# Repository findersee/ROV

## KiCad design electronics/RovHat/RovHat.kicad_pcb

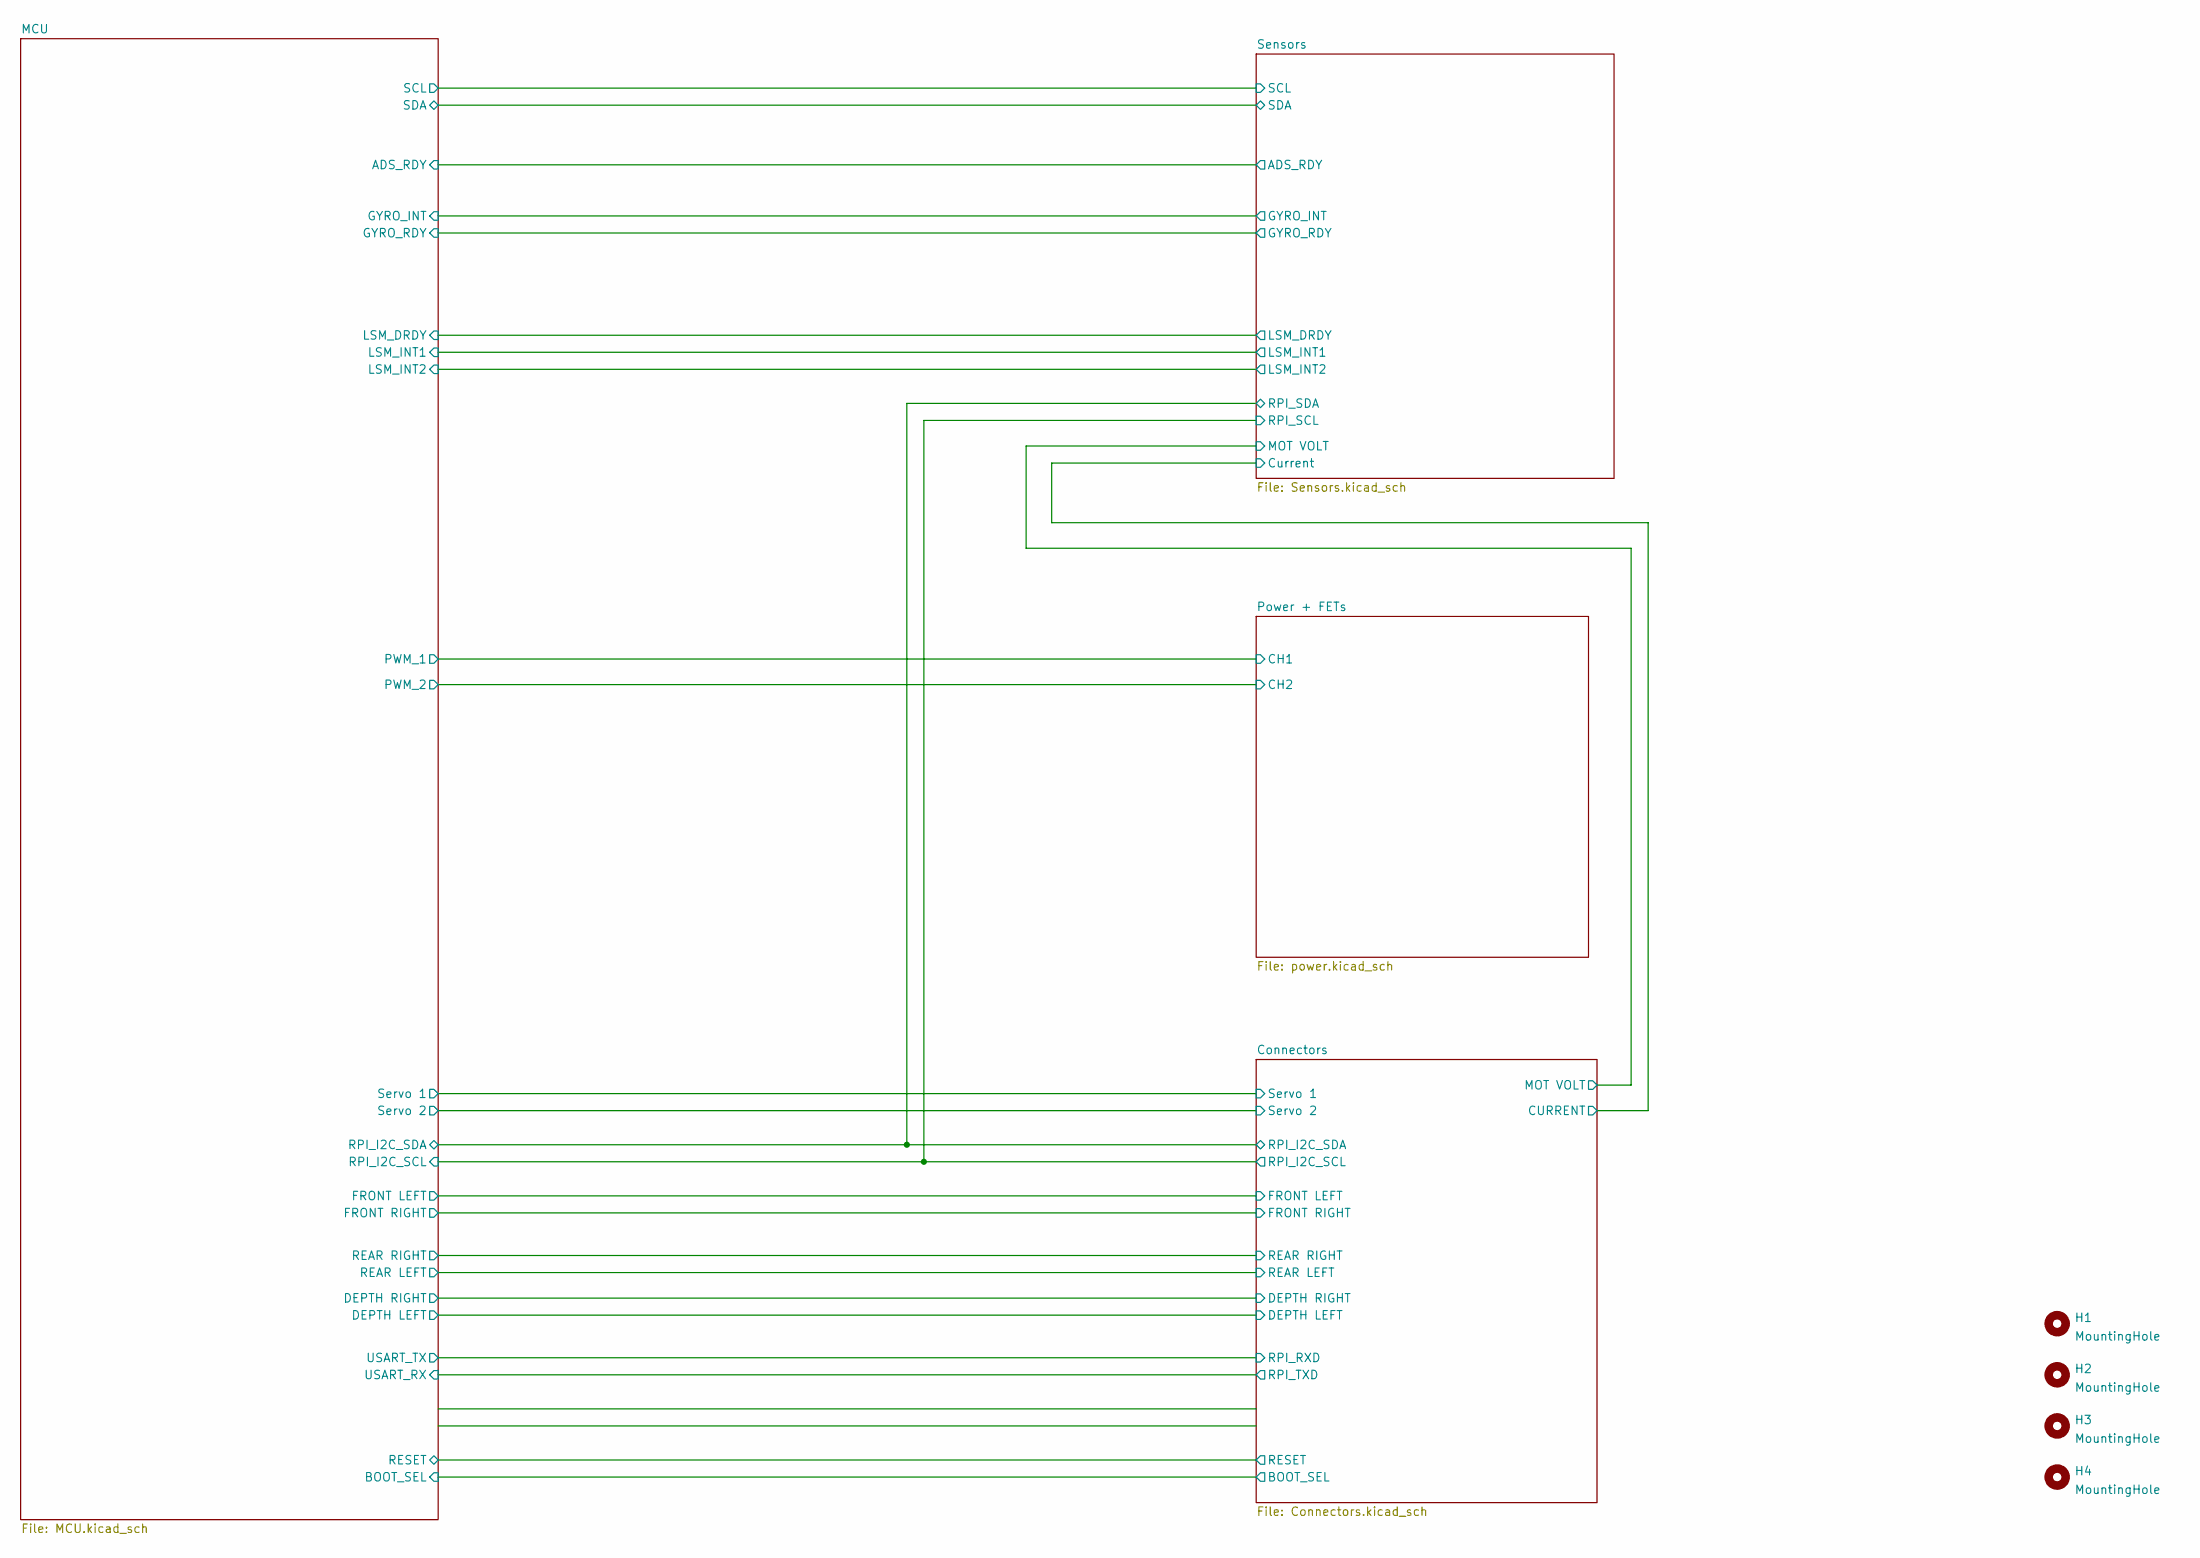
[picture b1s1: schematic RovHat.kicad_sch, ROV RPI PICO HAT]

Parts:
H1, H2, H3, H4: MountingHole; MountingHole_2.7mm_M2.5

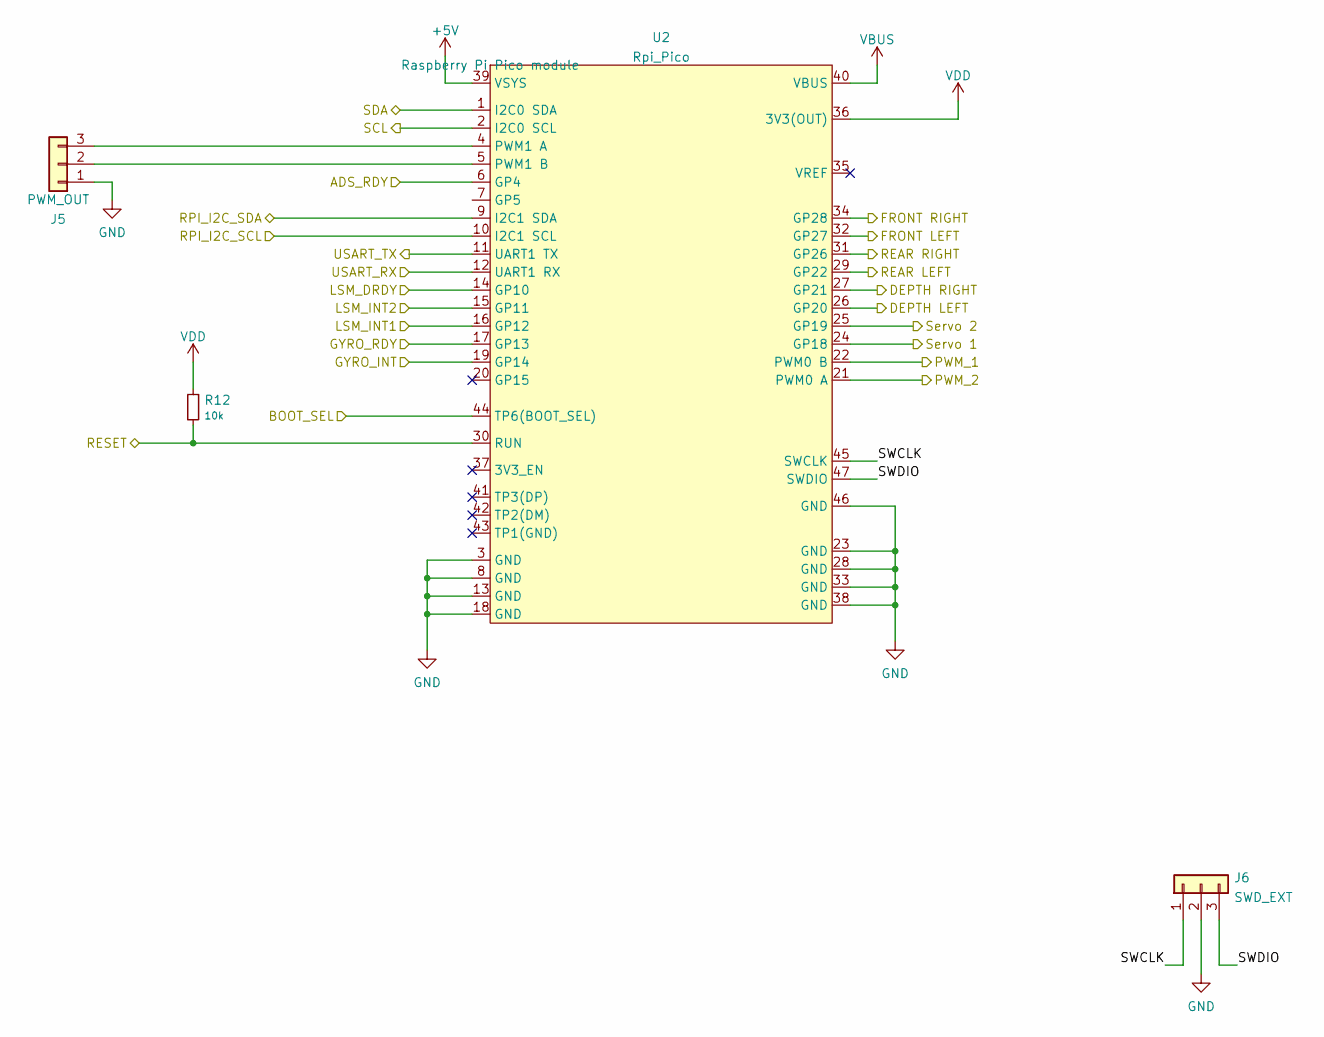
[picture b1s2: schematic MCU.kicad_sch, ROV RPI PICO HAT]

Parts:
J5: PWM_OUT; PinHeader_1x03_P2.54mm_Vertical
J6: SWD_EXT; JST_SH_BM03B-SRSS-TB_1x03-1MP_P1.00mm_Vertical
R12: 10k; R_0603_1608Metric
U2: Rpi_Pico; RP_PICO

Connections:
+5V: U2.39 (VSYS); also elsewhere on the board
/Connectors/BOOT_SEL: U2.44 (TP6(BOOT_SEL)); also elsewhere on the board
/Connectors/DEPTH LEFT: U2.26 (GP20); also elsewhere on the board
/Connectors/DEPTH RIGHT: U2.27 (GP21); also elsewhere on the board
/Connectors/FRONT LEFT: U2.32 (GP27); also elsewhere on the board
/Connectors/FRONT RIGHT: U2.34 (GP28); also elsewhere on the board
/Connectors/REAR LEFT: U2.29 (GP22); also elsewhere on the board
/Connectors/REAR RIGHT: U2.31 (GP26); also elsewhere on the board
/Connectors/RESET: R12.2, U2.30 (RUN); also elsewhere on the board
/Connectors/RPI_I2C_SCL: U2.10 (I2C1 SCL); also elsewhere on the board
/Connectors/RPI_I2C_SDA: U2.9 (I2C1 SDA); also elsewhere on the board
/Connectors/RPI_RXD: U2.11 (UART1 TX); also elsewhere on the board
/Connectors/RPI_TXD: U2.12 (UART1 RX); also elsewhere on the board
/Connectors/Servo 1: U2.24 (GP18); also elsewhere on the board
/Connectors/Servo 2: U2.25 (GP19); also elsewhere on the board
/MCU/ADS_RDY: U2.6 (GP4); also elsewhere on the board
/MCU/GYRO_INT: U2.19 (GP14); also elsewhere on the board
/MCU/GYRO_RDY: U2.17 (GP13); also elsewhere on the board
/MCU/LSM_DRDY: U2.14 (GP10); also elsewhere on the board
/MCU/LSM_INT1: U2.16 (GP12); also elsewhere on the board
/MCU/LSM_INT2: U2.15 (GP11); also elsewhere on the board
/MCU/PWM_1: U2.22 (PWM0 B); also elsewhere on the board
/MCU/PWM_2: U2.21 (PWM0 A); also elsewhere on the board
/MCU/SWCLK: J6.1, U2.45 (SWCLK)
/MCU/SWDIO: J6.3, U2.47 (SWDIO)
/Sensors/SCL: U2.2 (I2C0 SCL); also elsewhere on the board
/Sensors/SDA: U2.1 (I2C0 SDA); also elsewhere on the board
GND: J5.1, J6.2, U2.3 (GND), U2.8 (GND), U2.13 (GND), U2.18 (GND), U2.23 (GND), U2.28 (GND), U2.33 (GND), U2.38 (GND), U2.46 (GND); also elsewhere on the board
unnamed: J5.2, U2.5 (PWM1 B)
unnamed: J5.3, U2.4 (PWM1 A)
VBUS: U2.40 (VBUS)
VDD: R12.1, U2.36 (3V3(OUT)); also elsewhere on the board

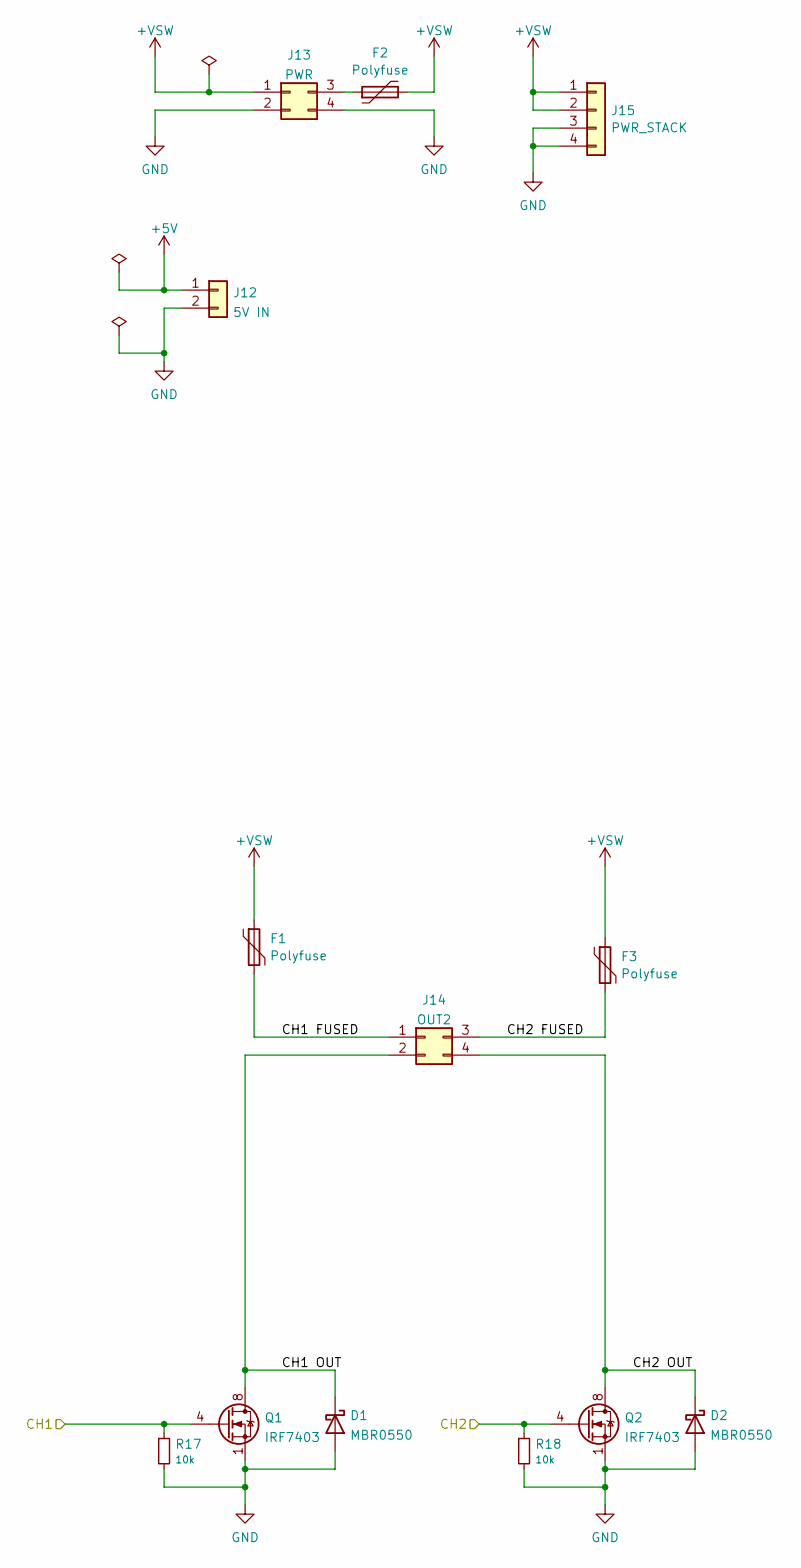
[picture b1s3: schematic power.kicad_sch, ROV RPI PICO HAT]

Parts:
D1, D2: MBR0550; D_SOD-123
F1, F2, F3: Polyfuse; Fuse_1206_3216Metric
J12: 5V IN; PinHeader_1x02_P2.54mm_Vertical
J13: PWR; PhoenixContact_MCV_1,5_4-G-3.5_1x04_P3.50mm_Vertical
J14: OUT2; PhoenixContact_MCV_1,5_4-G-3.5_1x04_P3.50mm_Vertical
J15: PWR_STACK; PinHeader_2x02_P2.54mm_Vertical
Q1, Q2: IRF7403; SOIC-8_3.9x4.9mm_P1.27mm
R17, R18: 10k; R_0603_1608Metric

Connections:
+5V: J12.1; also elsewhere on the board
+VSW: F1.1, F2.2, F3.1, J13.1, J15.1, J15.2
/MCU/PWM_1: Q1.4 (G), R17.1; also elsewhere on the board
/MCU/PWM_2: Q2.4 (G), R18.1; also elsewhere on the board
/Power + FETs/CH1 FUSED: F1.2, J14.1
/Power + FETs/CH1 OUT: D1.1 (K), J14.2, Q1.5 (D), Q1.6 (D), Q1.7 (D), Q1.8 (D)
/Power + FETs/CH2 FUSED: F3.2, J14.3
/Power + FETs/CH2 OUT: D2.1 (K), J14.4, Q2.5 (D), Q2.6 (D), Q2.7 (D), Q2.8 (D)
GND: D1.2 (A), D2.2 (A), J12.2, J13.2, J13.4, J15.3, J15.4, Q1.1 (S), Q1.2 (S), Q1.3 (S), Q2.1 (S), Q2.2 (S), Q2.3 (S), R17.2, R18.2; also elsewhere on the board
unnamed: F2.1, J13.3

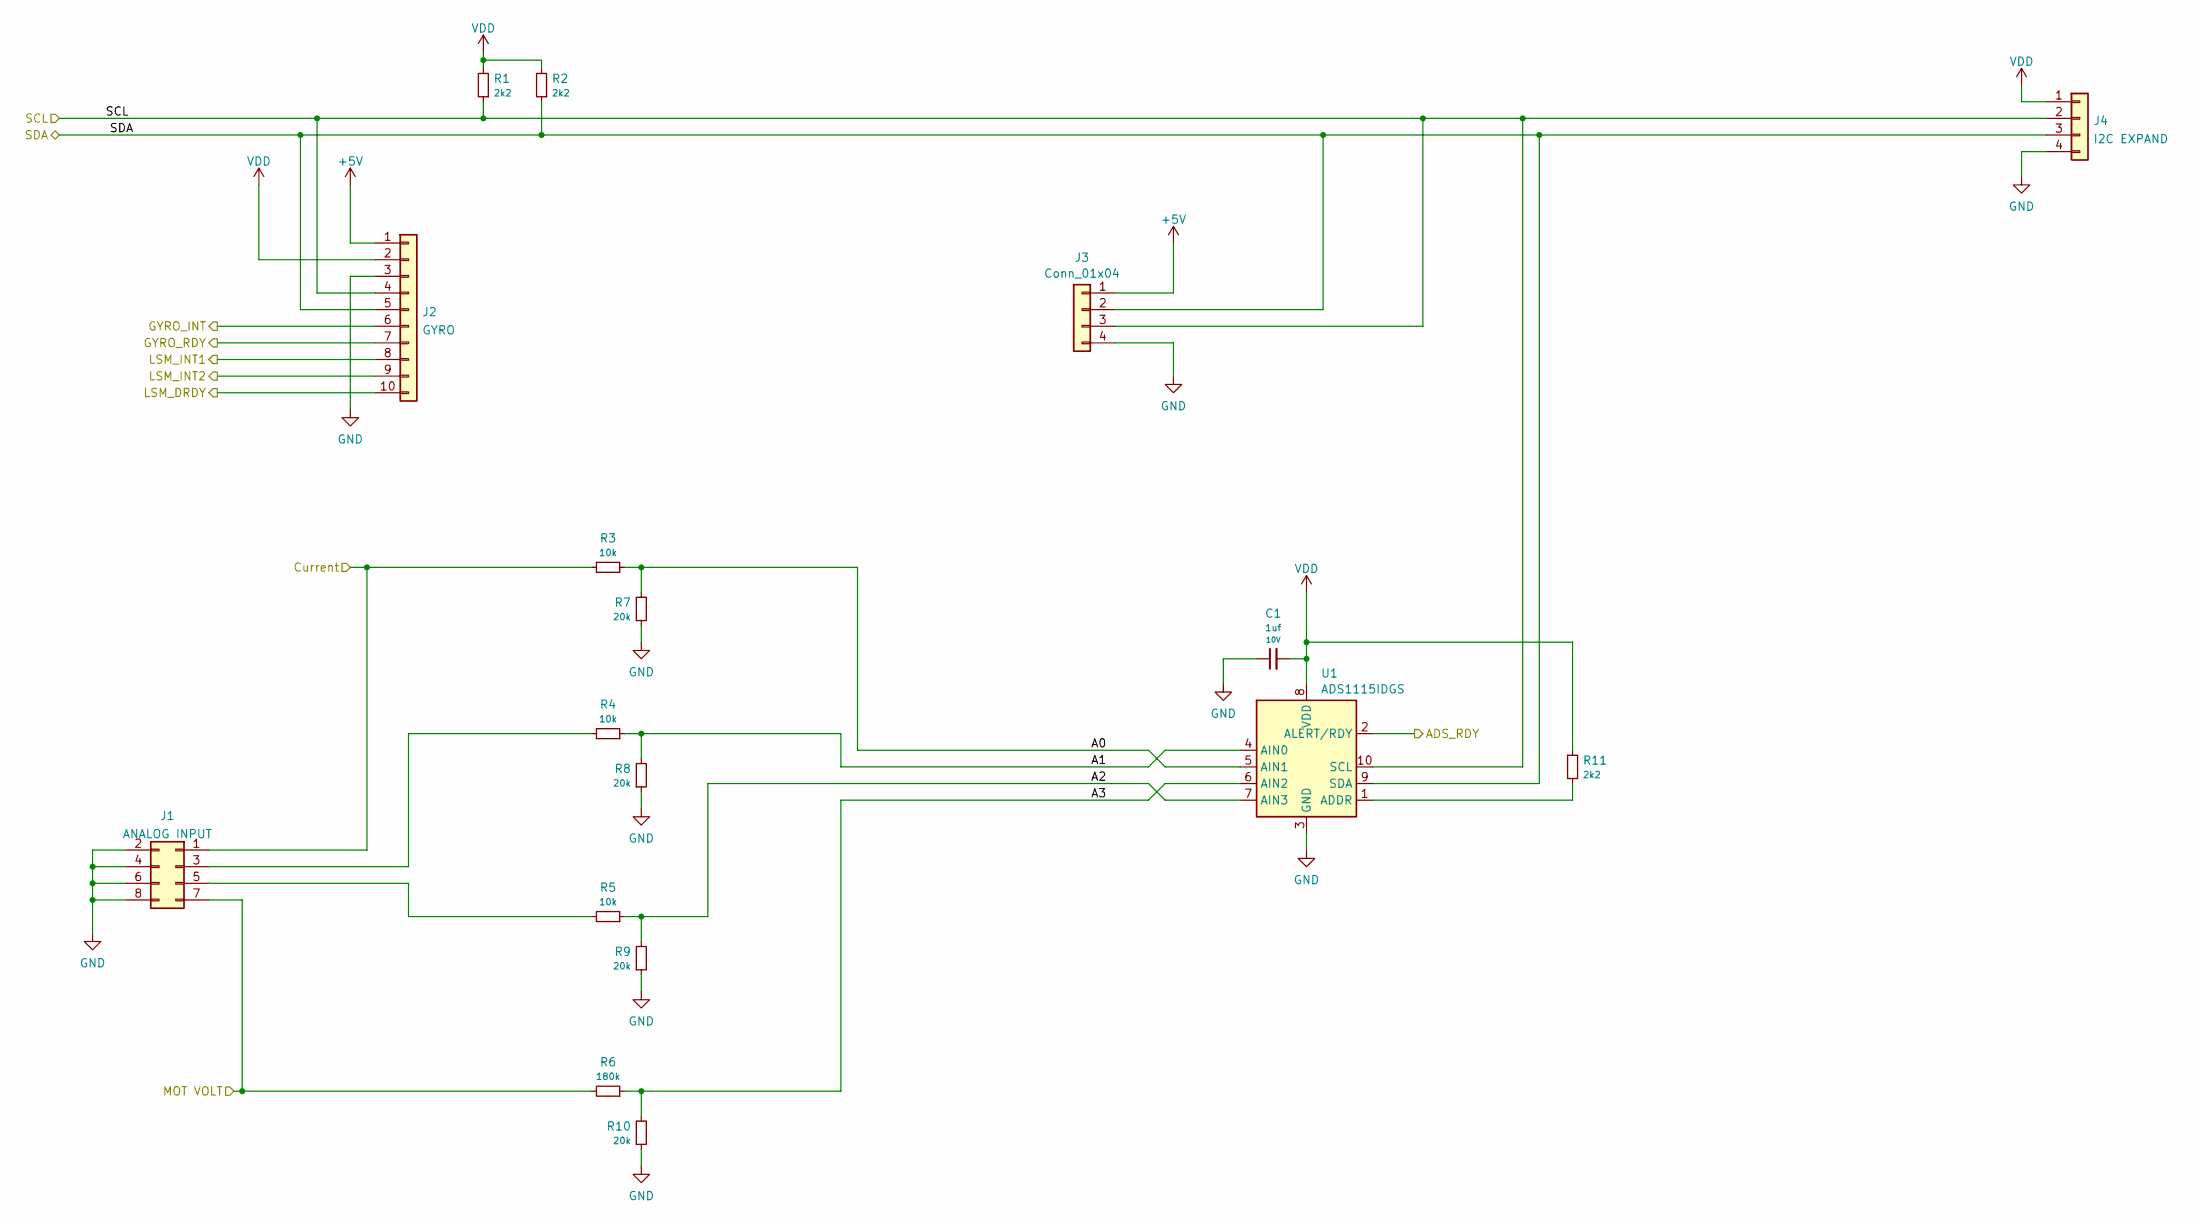
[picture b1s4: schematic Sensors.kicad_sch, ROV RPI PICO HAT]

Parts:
C1: 1uf; C_0603_1608Metric; Voltage 10V
J1: ANALOG INPUT; PinHeader_2x04_P2.54mm_Vertical
J2: GYRO; PinHeader_1x10_P2.54mm_Vertical
J3: Conn_01x04; Molex_PicoBlade_53398-0471_1x04-1MP_P1.25mm_Vertical
J4: I2C EXPAND; PinHeader_1x04_P2.54mm_Vertical
R1, R2, R11: 2k2; R_0603_1608Metric
R3, R4, R5: 10k; R_0603_1608Metric
R6: 180k; R_0603_1608Metric
R7, R8, R9, R10: 20k; R_0603_1608Metric
U1: ADS1115IDGS; TSSOP-10_3x3mm_P0.5mm

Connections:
+5V: J2.1, J3.1; also elsewhere on the board
/Connectors/CURRENT: J1.1, R3.2; also elsewhere on the board
/Connectors/MOT VOLT: J1.7, R6.2; also elsewhere on the board
/MCU/ADS_RDY: U1.2 (ALERT/RDY); also elsewhere on the board
/MCU/GYRO_INT: J2.6; also elsewhere on the board
/MCU/GYRO_RDY: J2.7; also elsewhere on the board
/MCU/LSM_DRDY: J2.10; also elsewhere on the board
/MCU/LSM_INT1: J2.8; also elsewhere on the board
/MCU/LSM_INT2: J2.9; also elsewhere on the board
/Sensors/A0: R3.1, R7.2, U1.5 (AIN1)
/Sensors/A1: R4.1, R8.2, U1.4 (AIN0)
/Sensors/A2: R5.1, R9.2, U1.7 (AIN3)
/Sensors/A3: R6.1, R10.2, U1.6 (AIN2)
/Sensors/SCL: J2.4, J3.3, J4.2, R1.1, U1.10 (SCL); also elsewhere on the board
/Sensors/SDA: J2.5, J3.2, J4.3, R2.1, U1.9 (SDA); also elsewhere on the board
GND: C1.1, J1.2, J1.4, J1.6, J1.8, J2.3, J3.4, J4.4, R7.1, R8.1, R9.1, R10.1, U1.3 (GND); also elsewhere on the board
unnamed: J1.3, R4.2
unnamed: J1.5, R5.2
unnamed: R11.2, U1.1 (ADDR)
VDD: C1.2, J2.2, J4.1, R1.2, R2.2, R11.1, U1.8 (VDD); also elsewhere on the board

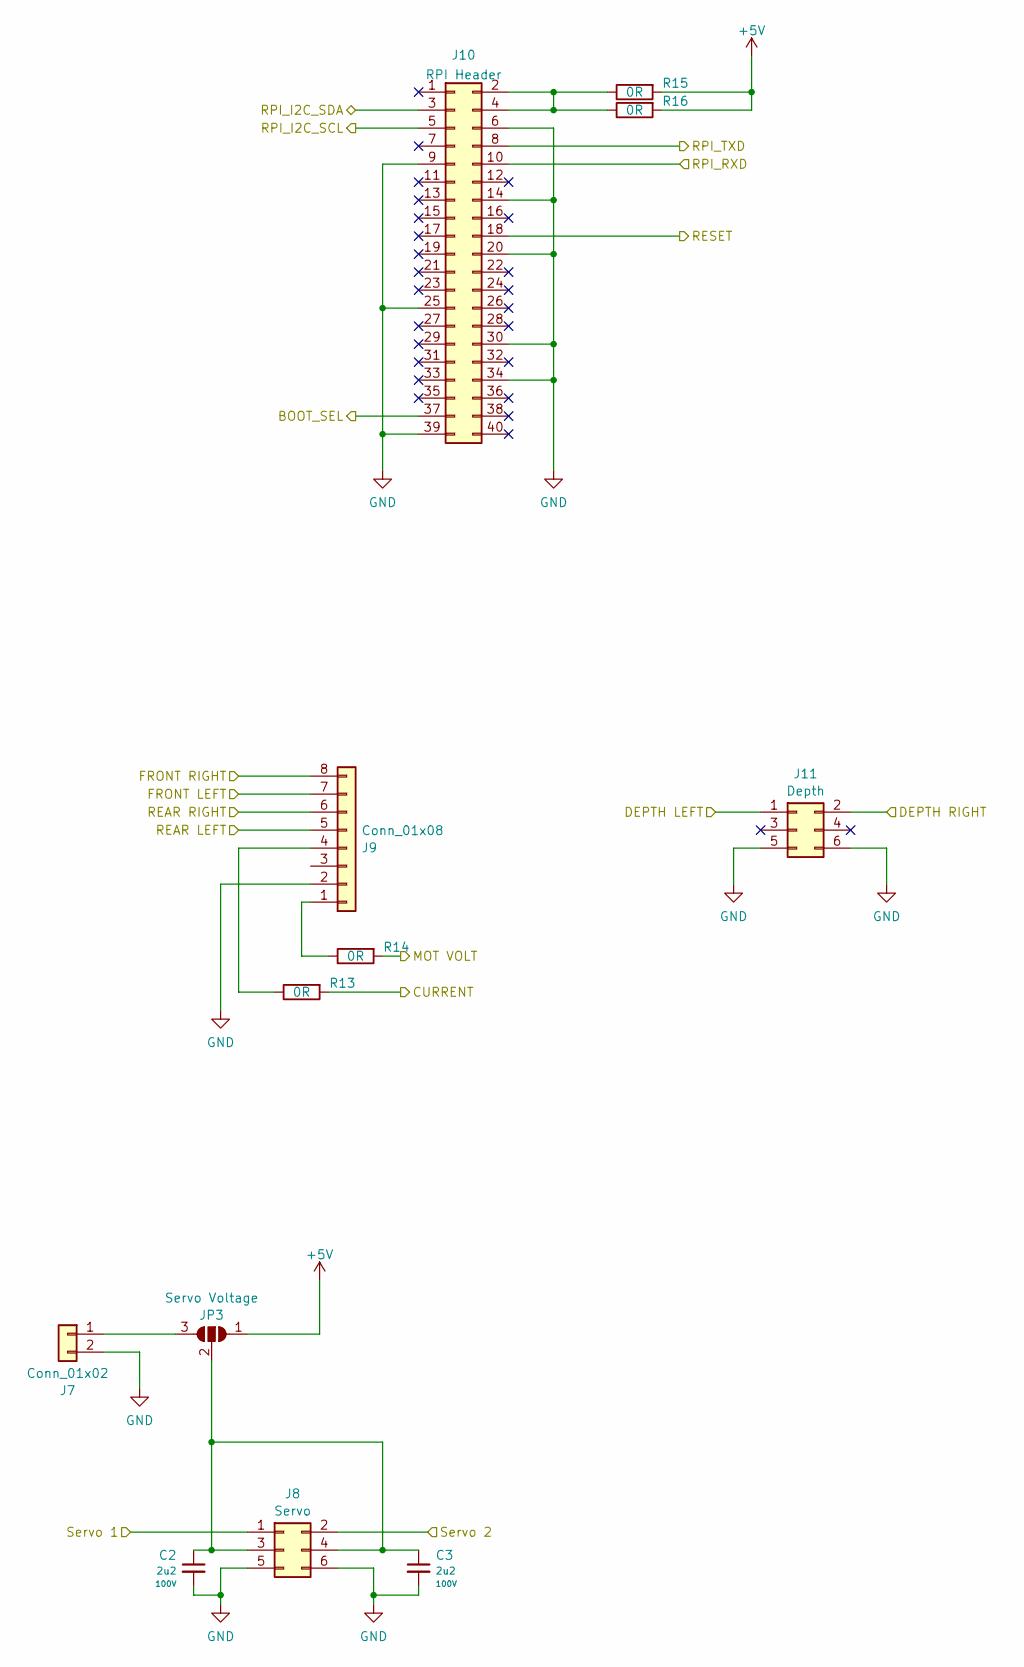
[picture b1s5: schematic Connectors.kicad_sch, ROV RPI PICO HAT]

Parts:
C2, C3: 2u2; C_0805_2012Metric; Voltage 100V
J7: Conn_01x02; PinHeader_2x01_P2.54mm_Vertical
J8: Servo; PinHeader_2x03_P2.54mm_Vertical
J9: Conn_01x08; JST_SH_SM08B-SRSS-TB_1x08-1MP_P1.00mm_Horizontal
J10: RPI Header; PinHeader_2x20_P2.54mm_Vertical
J11: Depth; PinHeader_2x03_P2.54mm_Vertical
JP3: Servo Voltage; 0402_Jumper_3pin
R13, R14, R15, R16: 0R; R_0603_1608Metric

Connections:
+5V: JP3.1 (A), R15.2, R16.2; also elsewhere on the board
/Connectors/BOOT_SEL: J10.37; also elsewhere on the board
/Connectors/CURRENT: R13.2; also elsewhere on the board
/Connectors/DEPTH LEFT: J11.1; also elsewhere on the board
/Connectors/DEPTH RIGHT: J11.2; also elsewhere on the board
/Connectors/FRONT LEFT: J9.7; also elsewhere on the board
/Connectors/FRONT RIGHT: J9.8; also elsewhere on the board
/Connectors/MOT VOLT: R14.2; also elsewhere on the board
/Connectors/REAR LEFT: J9.5; also elsewhere on the board
/Connectors/REAR RIGHT: J9.6; also elsewhere on the board
/Connectors/RESET: J10.18; also elsewhere on the board
/Connectors/RPI_I2C_SCL: J10.5; also elsewhere on the board
/Connectors/RPI_I2C_SDA: J10.3; also elsewhere on the board
/Connectors/RPI_RXD: J10.10; also elsewhere on the board
/Connectors/RPI_TXD: J10.8; also elsewhere on the board
/Connectors/Servo 1: J8.1; also elsewhere on the board
/Connectors/Servo 2: J8.2; also elsewhere on the board
GND: C2.2, C3.2, J7.2, J8.5, J8.6, J9.2, J10.6, J10.9, J10.14, J10.20, J10.25, J10.30, J10.34, J10.39, J11.5, J11.6; also elsewhere on the board
unnamed: J7.1, JP3.3 (B)
unnamed: C2.1, C3.1, J8.3, J8.4, JP3.2 (C)
unnamed: J9.1, R14.1
unnamed: J9.4, R13.1
unnamed: J10.2, J10.4, R15.1, R16.1

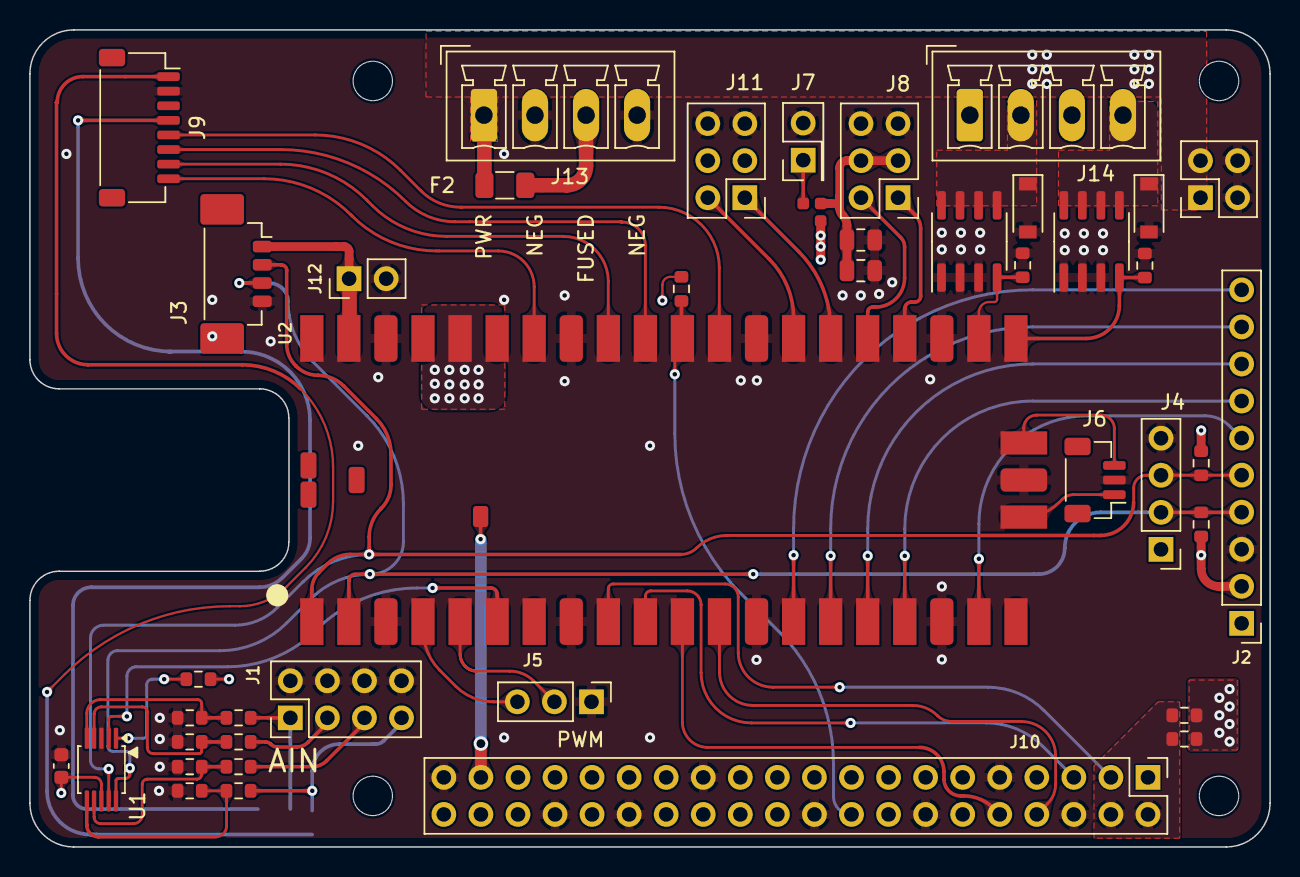
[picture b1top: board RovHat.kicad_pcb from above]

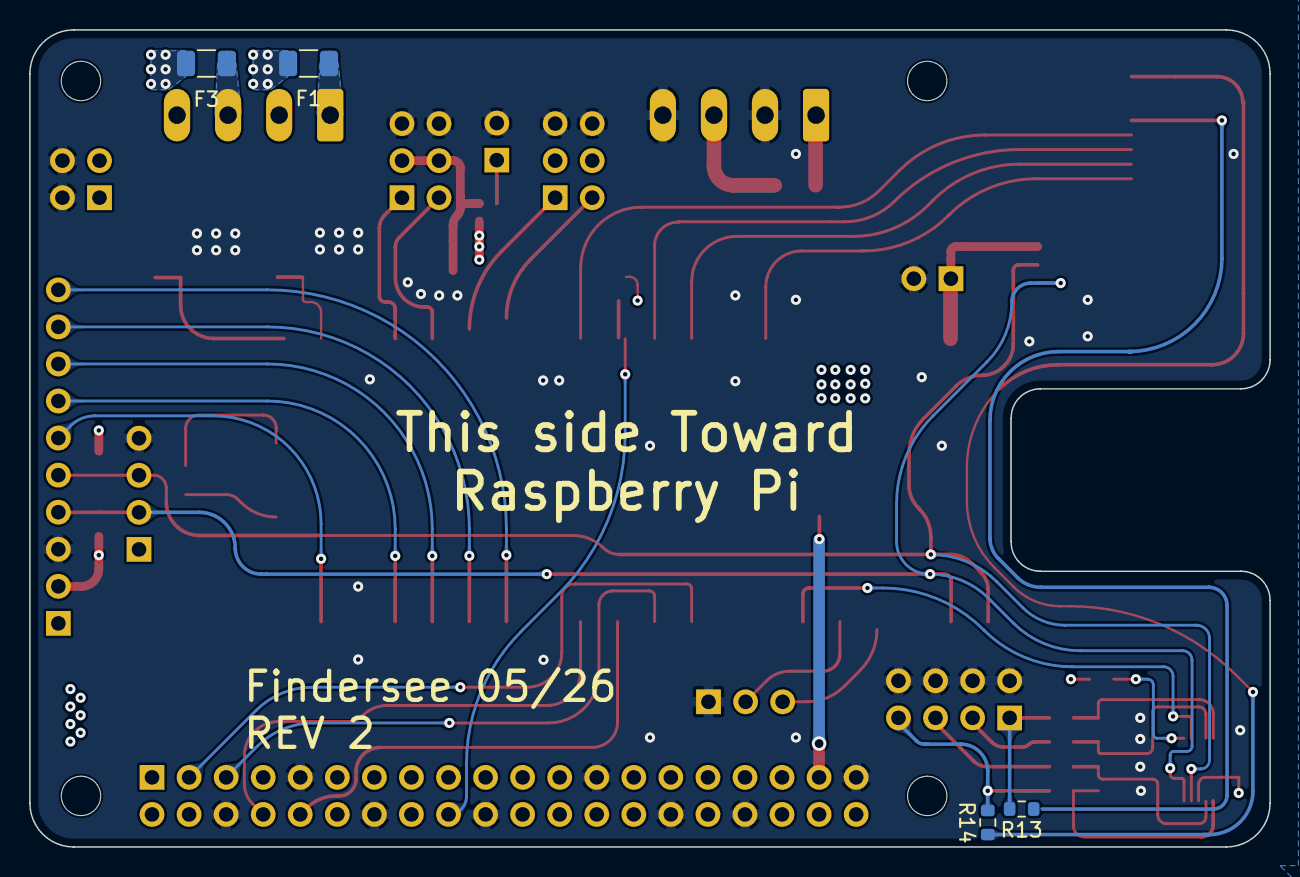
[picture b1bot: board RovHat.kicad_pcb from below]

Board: 4 copper layers, 85.0 x 56.0 mm, 50 parts (4 on the bottom side), 51 nets.

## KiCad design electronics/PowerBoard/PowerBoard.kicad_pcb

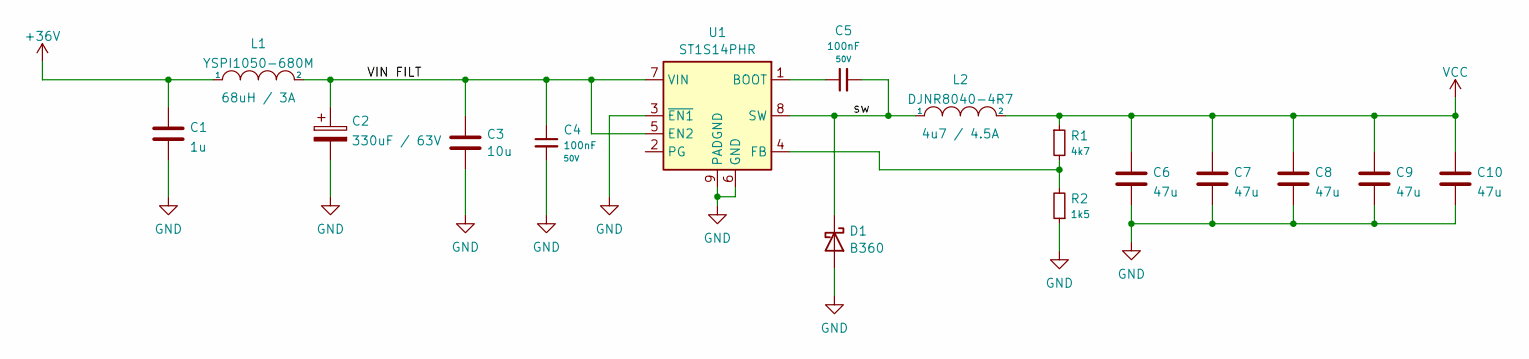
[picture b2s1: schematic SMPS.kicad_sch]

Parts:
C1: 1u; C_0805_2012Metric
C2: 330uF / 63V; CP_Elec_10x12.5
C3: 10u; C_0805_2012Metric
C4, C5: 100nF; C_0603_1608Metric; Voltage 50V
C6, C7, C8, C9, C10: 47u; C_0805_2012Metric
D1: B360; D_SMC
L1: YSPI1050-680M; YSPI1050; JLC C497902
L2: DJNR8040-4R7; IND_BOURNS_SRN8040; JLC C497902
R1: 4k7; R_0603_1608Metric
R2: 1k5; R_0603_1608Metric
U1: ST1S14PHR; TI_SO-PowerPAD-8

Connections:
+36V: C1.1, L1.1; also elsewhere on the board
/SMPS/VIN FILT: C2.1, C3.1, C4.1, L1.2, U1.5 (EN2), U1.7 (VIN)
/SMPS/sw: C5.2, D1.1 (K), L2.1, U1.8 (SW)
GND: C1.2, C2.2, C3.2, C4.2, C6.2, C7.2, C8.2, C9.2, C10.2, D1.2 (A), R2.1, U1.3 (~EN1), U1.6 (GND), U1.9 (PADGND); also elsewhere on the board
unnamed: C5.1, U1.1 (BOOT)
unnamed: R1.2, R2.2, U1.4 (FB)
VCC: C6.1, C7.1, C8.1, C9.1, C10.1, L2.2, R1.1; also elsewhere on the board

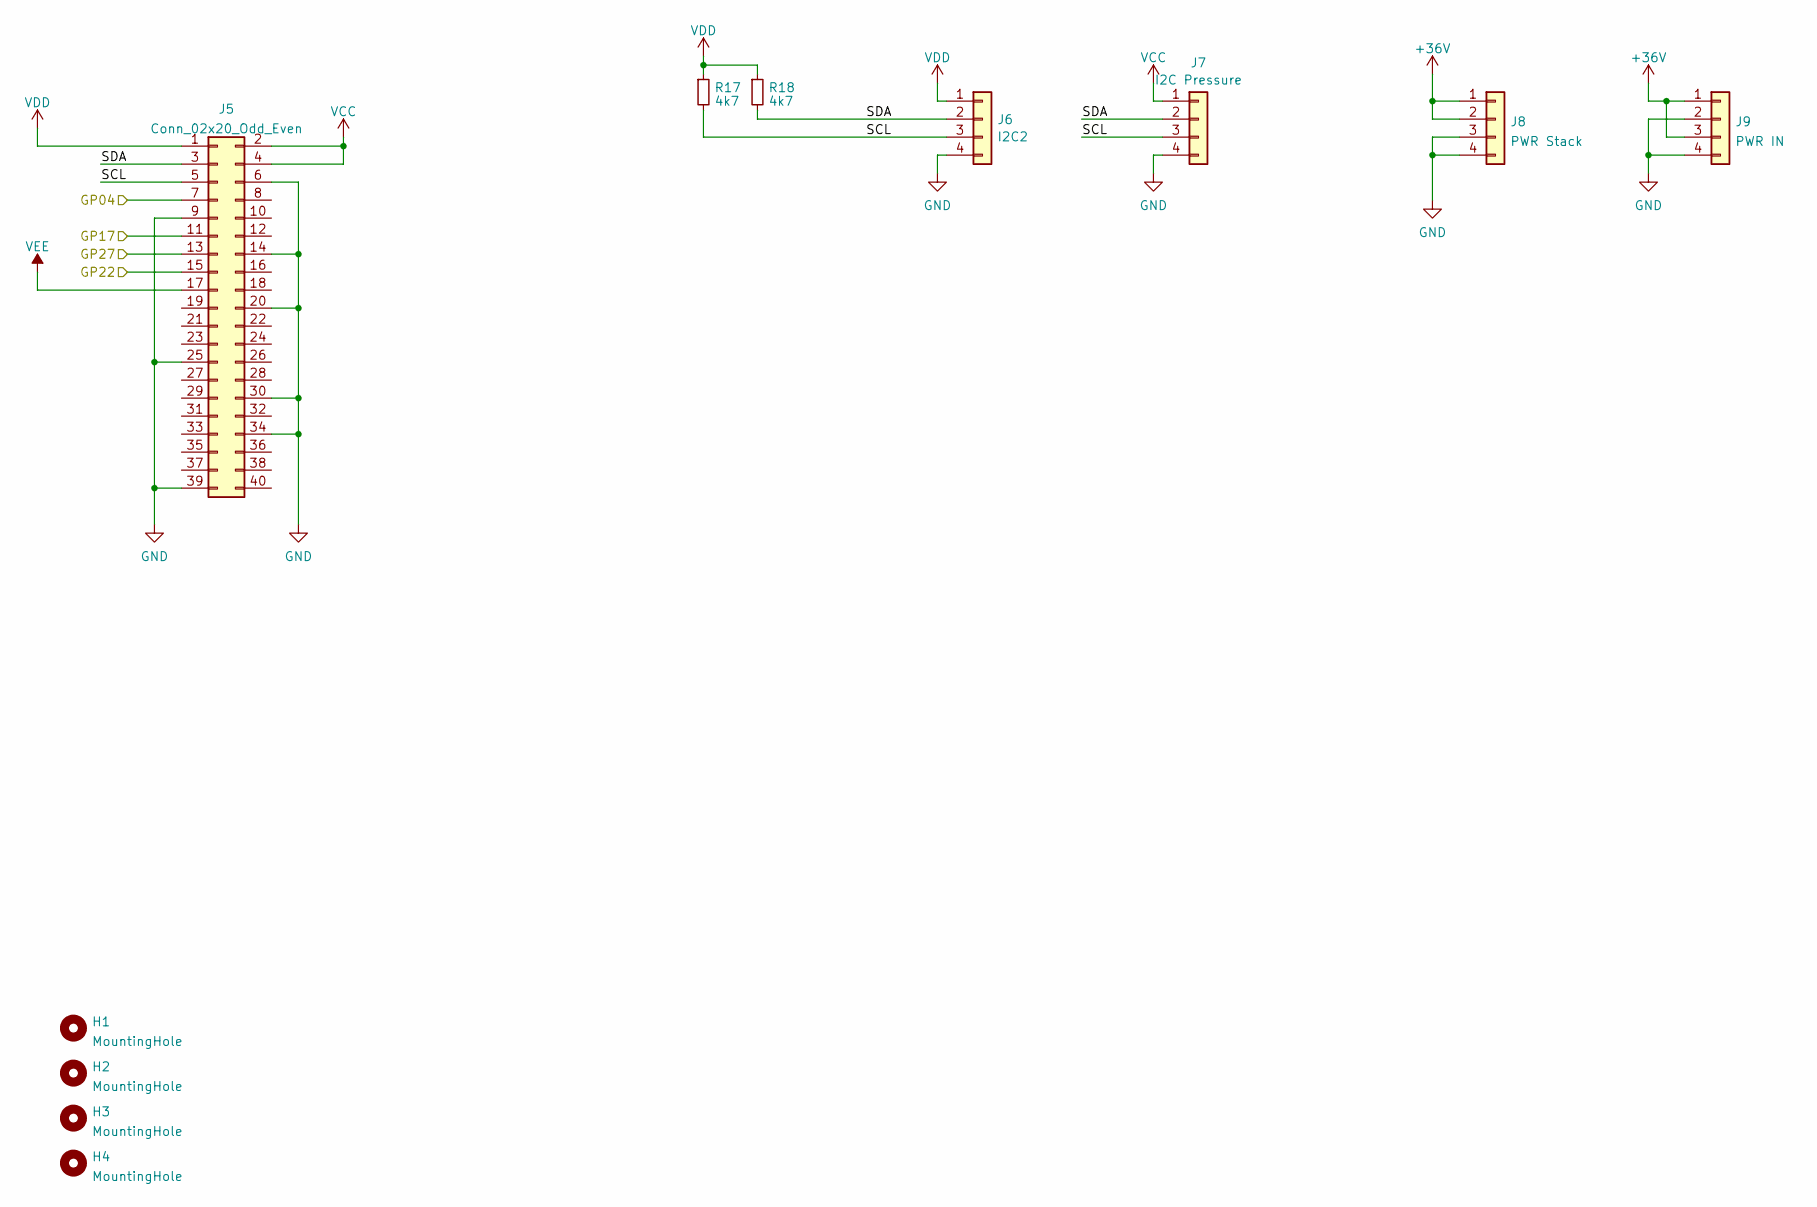
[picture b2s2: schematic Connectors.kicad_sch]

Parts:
H1, H2, H3, H4: MountingHole; MountingHole_2.7mm_M2.5
J5: Conn_02x20_Odd_Even; PinHeader_2x20_P2.54mm_Vertical
J6: I2C2; PinSocket_1x04_P2.54mm_Vertical
J7: I2C Pressure; Molex_PicoBlade_53398-0471_1x04-1MP_P1.25mm_Vertical
J8: PWR Stack; PinSocket_2x02_P2.54mm_Vertical
J9: PWR IN; PhoenixContact_MCV_1,5_4-G-3.5_1x04_P3.50mm_Vertical
R17, R18: 4k7; R_0603_1608Metric

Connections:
+36V: J8.1, J8.2, J9.1, J9.3; also elsewhere on the board
/Connectors/GP04: J5.7; also elsewhere on the board
/Connectors/GP17: J5.11; also elsewhere on the board
/Connectors/GP22: J5.15; also elsewhere on the board
/Connectors/GP27: J5.13; also elsewhere on the board
/Connectors/SCL: J5.5, J6.3, J7.3, R17.2
/Connectors/SDA: J5.3, J6.2, J7.2, R18.2
GND: J5.6, J5.9, J5.14, J5.20, J5.25, J5.30, J5.34, J5.39, J6.4, J7.4, J8.3, J8.4, J9.2, J9.4; also elsewhere on the board
VCC: J5.2, J5.4, J7.1; also elsewhere on the board
VDD: J5.1, J6.1, R17.1, R18.1; also elsewhere on the board
VEE: J5.17; also elsewhere on the board
